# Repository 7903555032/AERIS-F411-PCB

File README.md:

# AERIS-F411 Hardware
#AERIS — Advanced Embedded Research & Intelligent Systems

Professional STM32F411-based Embedded Development Board.

## Features

- STM32F411RET6
- USB Type-C
- SPI Flash
- microSD
- IMU
- Environmental Sensor
- CAN
- RS485
- SWD Debug

## Status

🚧 Under Development

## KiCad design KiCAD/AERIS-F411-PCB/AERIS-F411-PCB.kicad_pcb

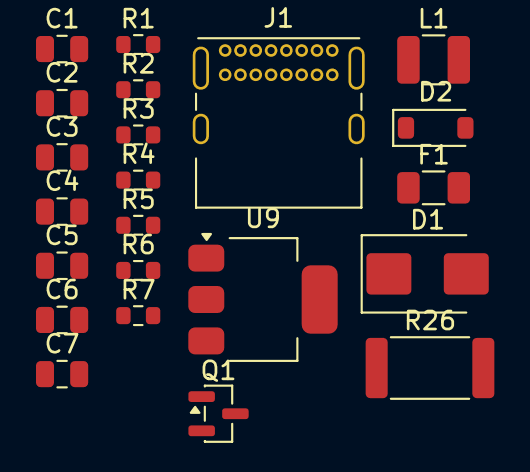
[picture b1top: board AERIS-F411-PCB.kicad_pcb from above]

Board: 2 copper layers, 22 parts (0 on the bottom side), 14 nets, no tracks yet.

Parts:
C1, C2, C5: 10uF; C_0805_2012Metric
C3, C6: 22uF; C_0805_2012Metric
C4: 100nF; C_0805_2012Metric
C7: 10nF; C_0805_2012Metric
D1: D_TVS; D_SMB
D2: D_Schottky; D_SOD-123
F1: Fuse; Fuse_1206_3216Metric
J1: USB_C_Receptacle_USB2.0_16P; USB_C_Receptacle_GCT_USB4085
L1: 4.7uH; L_1210_3225Metric
Q1: Q_PMOS_GSD; SOT-23
R1: 10K; R_0603_1608Metric
R2: 20K; R_0603_1608Metric
R3: 6.8K; R_0603_1608Metric
R4, R5: 22; R_0603_1608Metric
R6, R7: 5.1K; R_0603_1608Metric
R26: R_Shunt; R_2512_6332Metric
U9: AMS1117-3.3; SOT-223-3_TabPin2

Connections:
/POWER SECTION/3.3V: C6.1, U9.2 (VO)
/POWER SECTION/5V: C3.2, C5.1, D2.1 (K), L1.1, R2.1, U9.3 (VI)
/POWER SECTION/FB: R2.2, R3.1
/POWER SECTION/GND: C1.2, C2.1, C3.1, C5.2, C6.2, C7.2, D1.2 (A2), J1.A1 (GND), J1.A12 (GND), J1.B1 (GND), J1.B12 (GND), J1.SH (SHIELD), R1.2, R3.2, R6.1, R7.2, U9.1 (GND)
unnamed: D1.1 (A1), F1.2, R26.1
unnamed: D2.2 (A), J1.A4 (VBUS), J1.A9 (VBUS), J1.B4 (VBUS), J1.B9 (VBUS)
unnamed: J1.A5 (CC1), R6.2
unnamed: J1.B5 (CC2), R7.1
unnamed: J1.A6 (D+), J1.B6 (D+)
unnamed: J1.A7 (D-), J1.B7 (D-)
unnamed: Q1.1 (G), R1.1
unnamed: F1.1, Q1.2 (S)
unnamed: C4.1, L1.2
unnamed: C1.1, C2.2, R26.2
